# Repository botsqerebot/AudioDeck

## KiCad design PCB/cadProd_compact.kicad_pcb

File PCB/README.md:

# Music player PCB: next revision (rev 2)

Everything to change, check and test for rev 2. The main goal is power saving while the player is **off**:

|                  | Off current   | Shelf life on 1000 mAh                                                         |
| ---------------- | ------------- | ------------------------------------------------------------------------------ |
| Rev 1, estimated | ~0.6–1 mA     | ~6 weeks                                                                       |
| Rev 2, target    | **~25–30 µA** | well over a year (in practice the battery's own self-discharge sets the limit) |

The estimates come from datasheet typical values. Measure the real numbers at bring-up (section 6).

---

## 1. Power rails (the new design)

```
BAT ── BQ24074 ── +REG ──┬── TPS7A2033 "Digital_Vol" (EN = VIN, always on) ── AwO_D3v3 ──┬── ESP32-S3
                         │                                                                ├── BQ24074 EN2, pull-ups R9 R10 R11 R12
                         │                                                                └── Q2 AO3401A ── D3v3 (switched) ──┬── SD card + R6 R7
                         │                                                                                                    └── PCM5102 DVDD + CPVDD
                         └── TPS7A2033 "AnaVol" (EN = EN_ANAVOL) ── A3v3 (switched) ──┬── PCM5102 AVDD
                                                                                        └── MAX9722 amp
```

| Rail         | What's on it                                                              | On while the player is off?         |
| ------------ | ------------------------------------------------------------------------- | ----------------------------------- |
| **AwO_D3v3** | ESP32-S3, BQ24074 EN2, R9 (PGOOD), R10 (CHG), R11 (EN), R12 (BOOT)        | Yes                                 |
| **D3v3**     | SD card VDD, R6 (CMD), R7 (DAT0), PCM5102 DVDD (pin 20) and CPVDD (pin 1) | **No**, Q2 switches it off          |
| **A3v3**     | PCM5102 AVDD, MAX9722                                                     | **No**, `EN_ANAVOL` switches it off |

---

## 2. Changes already in the schematic

- [x] Digital regulator changed from MCP1825 to **TPS7A2033** (Iq ~6.5 µA instead of ~120 µA), with EN tied to VIN
- [x] **C24 1 µF** at the digital regulator's VIN
- [x] **C21/C22** (10 µF + 100 nF) at its output
- [x] Always-on rail **AwO_D3v3** split from the switched **D3v3**
- [x] **Q2 AO3401A** high-side switch, with R25 100k gate pull-up (off at boot and in sleep) and R26 10k to the GPIO
- [x] **R5** (SD Det pull-up, ~330 µA with a card in) **removed**. The firmware uses the internal pull-up while awake.
- [x] R6 and R7 (SD pull-ups) moved to switched D3v3, so they can't back-power the card
- [x] PCM5102 DVDD/CPVDD moved to switched D3v3
- [x] R9, R10, R11, R12 and BQ24074 EN2 on AwO_D3v3. EN on the switched rail would hold the ESP32 in reset forever.

---

## 3. Still to do in the schematic

### Must fix

- [x] **C23 (47 nF) from Q2 gate to Q2 source**, side by side with R25. This gives a ~0.5 ms turn-on (10k × 47 nF), so the inrush is about 75 mA instead of a dip that could reset the ESP32. (Gate-to-GND would switch D3v3 on briefly at every power-up.)
- [ ] **Connect the `GPIO` label at R26 to a real pin: IO21 (module pad 23).** IO11 (pad 19), IO12 (pad 20) and IO18 (pad 11) are also free. Avoid the strapping pins IO0, IO3, IO45 and IO46.
- [ ] **Give the two `GPIO` labels separate names.** Same-named labels are one net in KiCad. Use `BAT_SENSE` → IO8 (pad 12) and `D3V3_EN` → IO21 (pad 23).
- [x] **Battery divider on IO8 (module pad 12)** (R5/R27 1 MΩ, C25 100 nF). It's needed for battery %, LED4 (above 60 %) and the low-battery warnings:
    ```
    BAT+ ──[1 MΩ]──┬── IO8
                   ├──[1 MΩ]── GND
                   └──[100 nF]── GND
    ```
    It draws about 2 µA. IO8 is on ADC1.
- [ ] **Make thermal refes for the `GND` on `LEDs` and Battery**
- [ ] **Battery connector** Make the battery connector fit a JST connection

### Check against datasheets

- [ ] **BQ24074 TMR (pin 14) and ITERM (pin 15)** are unconnected. Check what that means for the safety timer and the termination current, and tie them as intended.
- [ ] **BQ24074 TS:** R8 is a fixed 10k to GND, so temperature protection is off. For a LiPo in a closed case, consider a pack with a 10k NTC wired to TS.
- [ ] **TPS7A2033 output capacitance:** confirm that 10 µF + 100 nF on each output is within the stable range. It should be.
- [ ] **AO3401A pinout in the footprint:** 1 = Gate, 2 = Source, 3 = Drain (SOT-23).

### LEDs

- [ ] **Make the schematic and firmware agree on the colours.** Right now they don't:

    | GPIO | Net  | Schematic | Firmware `config.h` |
    | ---- | ---- | --------- | ------------------- |
    | 38   | LED1 | D1 red    | green               |
    | 39   | LED2 | D2 orange | purple              |
    | 40   | LED3 | D3 green  | orange              |
    | 41   | LED4 | D4 purple | blue                |
    | 42   | LED5 | D5 blue   | red                 |

    Decide which colour goes where, then make the schematic, the silkscreen and `config.h` match.

- [ ] Optional: change R13–R21 from 1 kΩ to **2.2–4.7 kΩ**. That's about 1 mA per LED now; higher values are usually still bright enough behind a case.

### Optional

- [ ] **External 1 MΩ pull-up on PLAY** to AwO_D3v3. The firmware could then power down the RTC peripherals in deep sleep, saving a few µA.
- [ ] **MAX17048 fuel gauge** on I2C (e.g. IO11/IO12), if the divider's ~±10 % isn't good enough. It stays accurate while charging and under load, and draws ~4 µA in hibernate. It needs a firmware driver.
- [ ] Remove any leftover symbols that have no footprint (the old AP2112K symbol).

---

## 4. Footprints and BOM

- [ ] **Digital_Vol:** SOT-23-5 for the TPS7A2033 (it was the MCP1825's SOT-223/DDPAK). Pins: 1 VIN, 2 GND, 3 EN, 4 NC, 5 VOUT.
- [ ] **Q2:** SOT-23. Add **C23** and **C24** footprints.
- [ ] **The BOM says µF**, not "yF". KiCad shows µ as y on some values.
- [ ] TPS7A2033 ×2 (digital + analog). The MCP1825 is no longer used.
- [ ] Battery divider: 2 × 1 MΩ, 1 × 100 nF (0402/0603).

---

## 5. Layout

- [ ] **C24** right next to the digital TPS7A2033's VIN pin. **C21/C22** right next to its VOUT.
- [ ] **C23** close to Q2, between its gate and source pads.
- [ ] Keep the ESP32's decoupling (C6, C7, C8) right at the module's 3V3 pin.
- [ ] **C1/C2** (SD decoupling) close to the SD socket, on D3v3.
- [ ] Battery divider close to IO8, away from the I2S and SD clock traces. The 1 MΩ node is high-impedance and picks up noise.
- [ ] Short, wide traces from Q2 to the SD card VDD.

---

## 6. Bring-up tests

1. **Rails:** power from the battery only. AwO_D3v3 should be 3.3 V. **D3v3 and A3v3 should be 0 V** until the firmware turns them on.
2. **Boot:** the ESP32 starts every time (if it doesn't, EN/R11 is on the wrong rail). Hold Play for 3 s to turn on.
3. **Inrush:** with a scope on AwO_D3v3, the firmware switches D3v3 on. The dip must stay above about 3.0 V, and the ESP32 must not reset.
4. **SD and audio:** cards mount, music plays, and there's no pop at power-on.
5. **Off current:** power off, then put a multimeter (µA range) in series with the battery. Target **~25–30 µA**. If it's much higher:
    - Is D3v3 really 0 V?
    - Is any ESP32 pin driving high into the SD card or DAC?
    - Are the LEDs off?
6. **Charging:** plug in USB. The orange LED lights while charging, also while the player is off. Unplugged, there's no wake loop.
7. **Battery %:** compare Settings > Battery with a multimeter on BAT+ (around 4.2 V full, 3.7 V about 50 %).
8. **LEDs:** check each colour against the table in section 3.

---

## 7. Firmware changes needed for rev 2

These go into `flac_player_4/flac_player/` once the board exists. They're not done yet; ask when the GPIO is final.

- [ ] `config.h`: new `PIN_D3V3_EN 21` (or whichever pin you choose). LOW = D3v3 on.
- [ ] Boot: drive `PIN_D3V3_EN` LOW, wait ~5 ms, then start the SD card.
- [ ] Before deep sleep: drive **all** SD pins (CS, CLK, MOSI, MISO) and I2S pins **LOW**, then set `PIN_D3V3_EN` HIGH and hold it.
    - Rev 1 holds SD CS _high_ in sleep. On rev 2 that would push current into the unpowered card through its protection diodes.
- [ ] `PIN_BAT_ADC 8`. This turns on Settings > Battery, LED4 above 60 %, the red low-battery LED and the "Battery low" / "Battery critical" warnings. That code is already written.
- [ ] LED pin colours in `config.h` to match section 3.

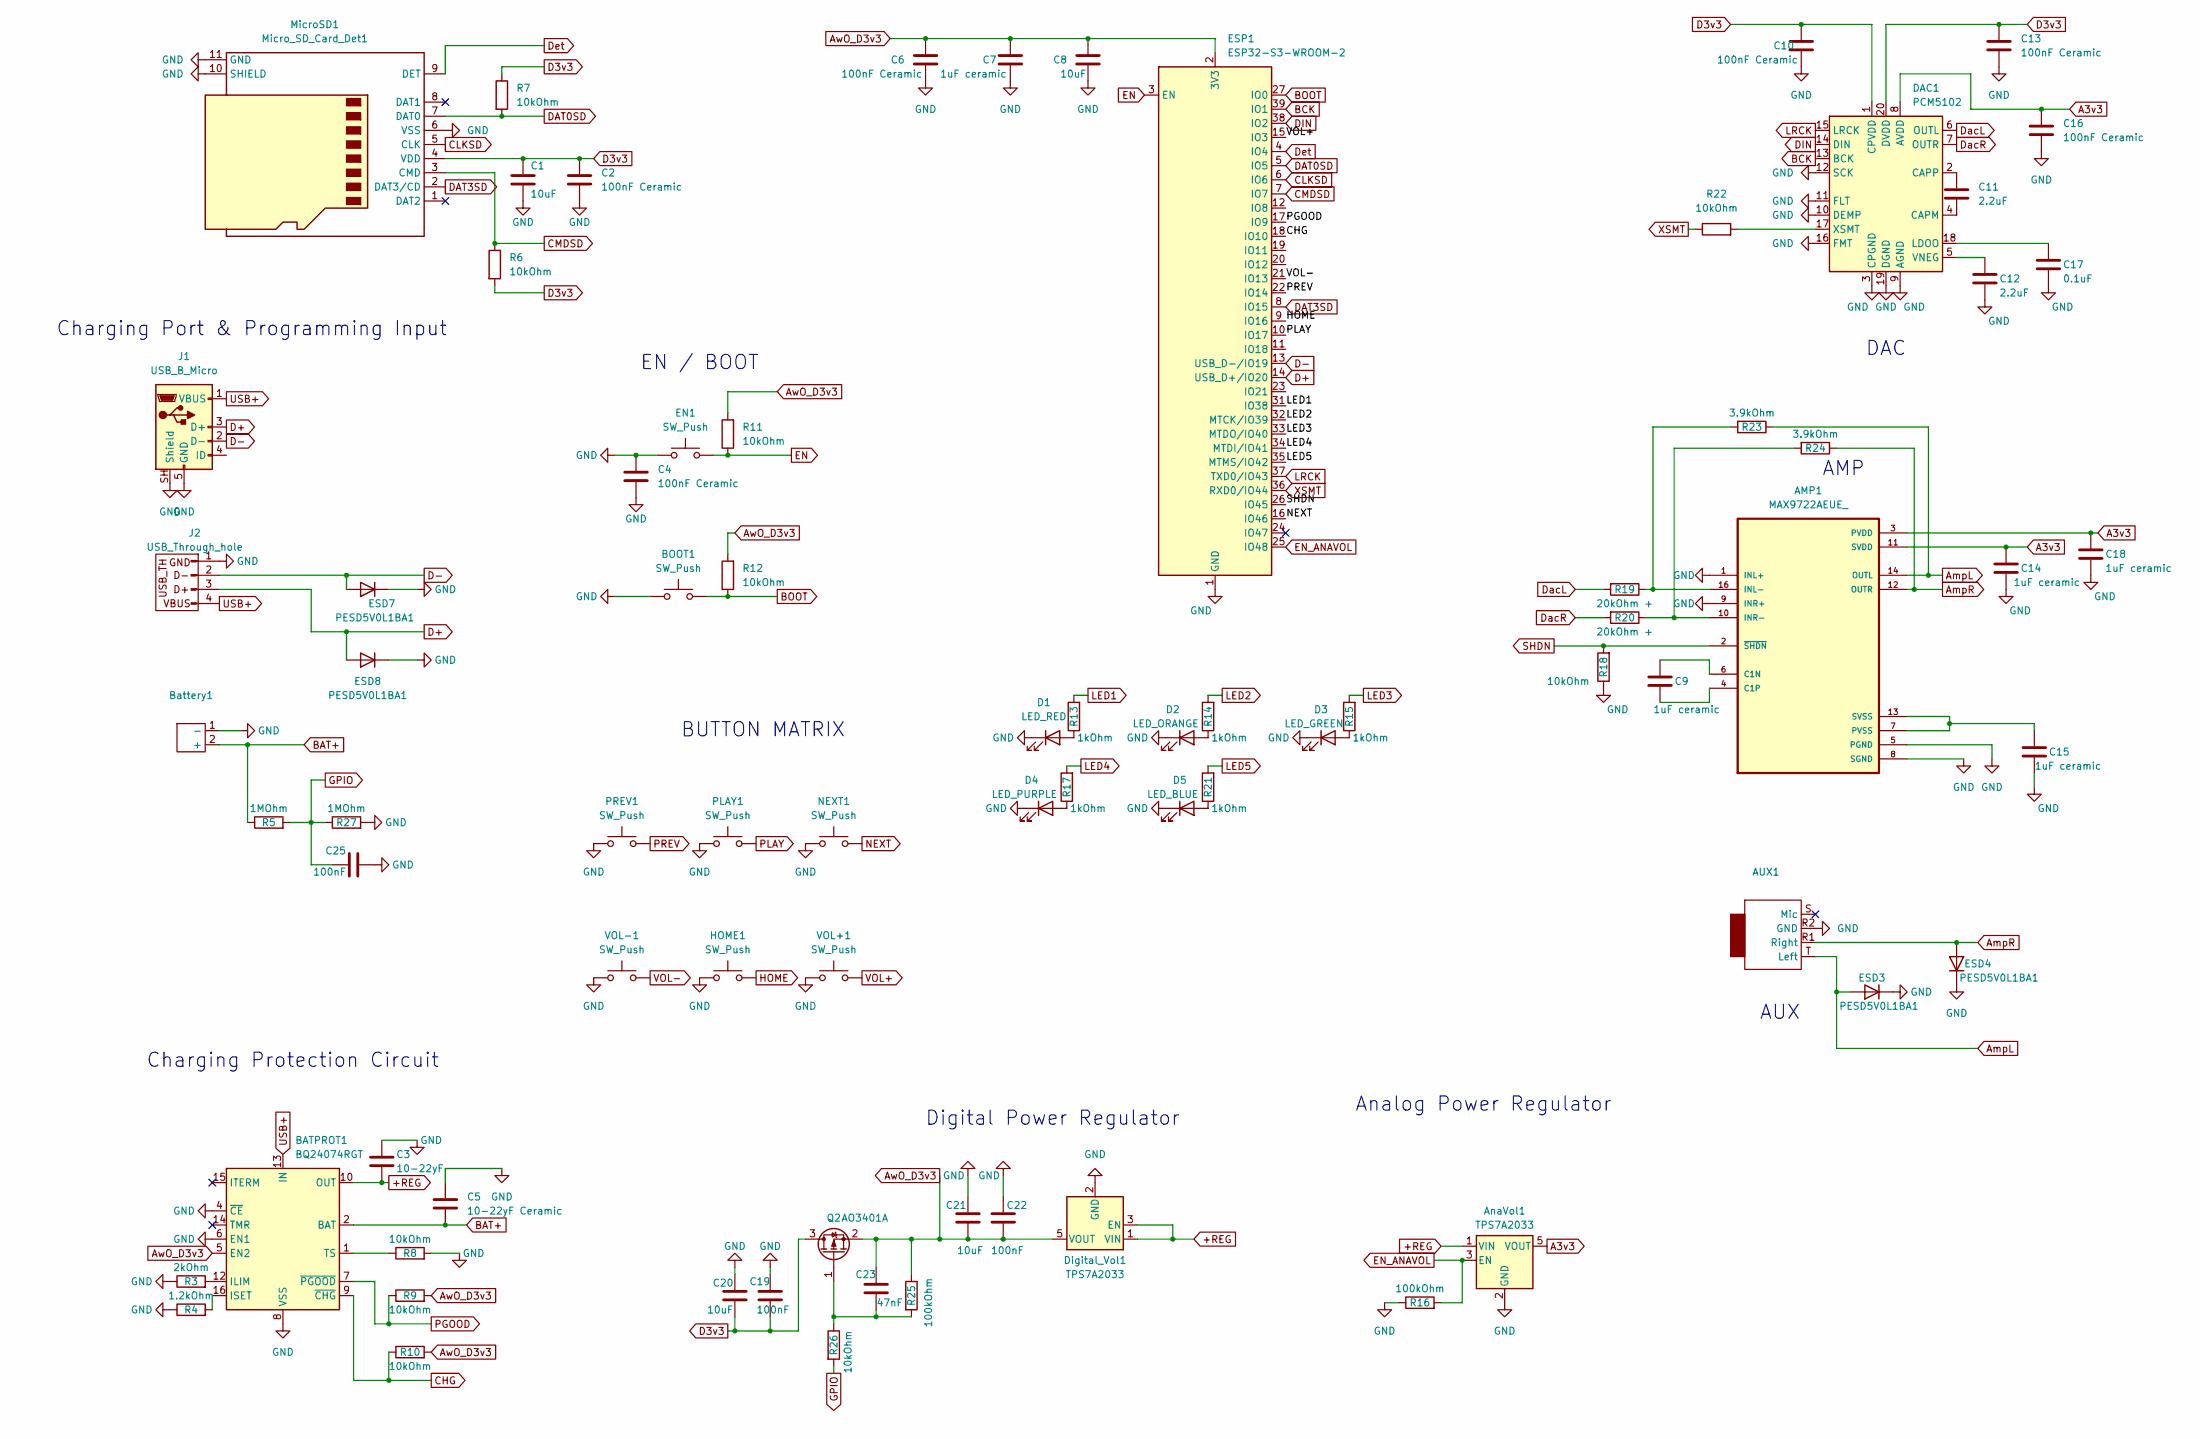
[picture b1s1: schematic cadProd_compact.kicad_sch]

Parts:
AMP1: MAX9722AEUE_; SOP65P640X110-16N
AUX1: Jack_3.5mm_PJ320D_Horizontal
AnaVol1: TPS7A2033; SOT-23-5
BATPROT1: BQ24074RGT; VQFN-16-1EP_3x3mm_P0.5mm_EP1.8x1.8mm
BOOT1: SW_Push; SW_Push_SPST_NO_Alps_SKRK
Battery1: JST_PH_B2B-PH-K_1x02_P2.00mm_Vertical
C1, C8, C20, C21: 10uF; C_0805_2012Metric_Pad1.18x1.45mm_HandSolder
C2, C4, C6, C10, C13, C16: 100nF Ceramic; C_0805_2012Metric_Pad1.18x1.45mm_HandSolder
C3: 10-22yF; C_0805_2012Metric_Pad1.18x1.45mm_HandSolder
C5: 10-22yF Ceramic; C_0805_2012Metric_Pad1.18x1.45mm_HandSolder
C7, C9, C14, C15, C18: 1uF ceramic; C_0805_2012Metric_Pad1.18x1.45mm_HandSolder
C11, C12: 2.2uF; C_0805_2012Metric_Pad1.18x1.45mm_HandSolder
C17: 0.1uF; C_0805_2012Metric_Pad1.18x1.45mm_HandSolder
C19, C22, C25: 100nF; C_0805_2012Metric_Pad1.18x1.45mm_HandSolder
C23: 47nF; C_0805_2012Metric_Pad1.18x1.45mm_HandSolder
D1: LED_RED; LED_0805_2012Metric_Pad1.15x1.40mm_HandSolder
D2: LED_ORANGE; LED_0805_2012Metric_Pad1.15x1.40mm_HandSolder
D3: LED_GREEN; LED_0805_2012Metric_Pad1.15x1.40mm_HandSolder
D4: LED_PURPLE; LED_0805_2012Metric_Pad1.15x1.40mm_HandSolder
D5: LED_BLUE; LED_0805_2012Metric_Pad1.15x1.40mm_HandSolder
DAC1: PCM5102; TSSOP-20_4.4x6.5mm_P0.65mm
Digital_Vol1: TPS7A2033; SOT-23-5
EN1: SW_Push; SW_Push_SPST_NO_Alps_SKRK
ESD3, ESD4, ESD7, ESD8: PESD5V0L1BA1; D_SOD-323
ESP1: ESP32-S3-WROOM-2
HOME1: SW_Push; SW_SPST_SKQG_WithStem
J1: USB_B_Micro; USB_Micro-B_Wuerth_629105150521
J2: USB_Through_hole; PinHeader_1x04_P2.54mm_Vertical_USB
MicroSD1: Micro_SD_Card_Det1; microSD_HC_Hirose_DM3AT-SF-PEJM5
NEXT1: SW_Push; SW_SPST_SKQG_WithStem
PLAY1: SW_Push; SW_SPST_SKQG_WithStem
PREV1: SW_Push; SW_SPST_SKQG_WithStem
Q2: AO3401A; SOT-23
R3: 2kOhm; R_0805_2012Metric_Pad1.20x1.40mm_HandSolder
R4: 1.2kOhm; R_0805_2012Metric_Pad1.20x1.40mm_HandSolder
R5, R27: 1MOhm; R_0805_2012Metric_Pad1.20x1.40mm_HandSolder
R6, R7, R8, R9, R10, R11, R12, R18, R22, R26: 10kOhm; R_0805_2012Metric_Pad1.20x1.40mm_HandSolder
R13, R14, R15, R17, R21: 1kOhm; R_0805_2012Metric_Pad1.20x1.40mm_HandSolder
R16, R25: 100kOhm; R_0805_2012Metric_Pad1.20x1.40mm_HandSolder
R19, R20: 20kOhm +; R_0805_2012Metric_Pad1.20x1.40mm_HandSolder
R23, R24: 3.9kOhm; R_0805_2012Metric_Pad1.20x1.40mm_HandSolder
VOL+1: SW_Push; SW_SPST_SKQG_WithStem
VOL-1: SW_Push; SW_SPST_SKQG_WithStem

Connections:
+REG: AnaVol1.1 (VIN), BATPROT1.10 (OUT), BATPROT1.11 (OUT), C3.2, Digital_Vol1.1 (VIN), Digital_Vol1.3 (EN)
A3v3: AMP1.3 (PVDD), AMP1.11 (SVDD), AMP1.15 (SVDD), AnaVol1.5 (VOUT), C14.1, C16.1, C18.1, DAC1.8 (AVDD); also elsewhere on the board
AmpL: AMP1.14 (OUTL), AUX1.T (Left), ESD3.2 (A), R23.1
AmpR: AMP1.12 (OUTR), AUX1.R1 (Right), ESD4.2 (A), R24.1
AwO_D3v3: BATPROT1.5 (EN2), C6.1, C7.1, C8.1, C21.2, C22.2, C23.1, Digital_Vol1.5 (VOUT), ESP1.2 (3V3), Q2.2 (S), R9.2, R10.2, R11.2, R12.2, R25.1
BAT+: BATPROT1.2 (BAT), BATPROT1.3 (BAT), Battery1.2 (+), C5.2, R5.1
BCK: DAC1.13 (BCK), ESP1.39 (IO1)
BOOT: BOOT1.2, ESP1.27 (IO0), R12.1
CHG: BATPROT1.9 (~CHG), ESP1.18 (IO10), R10.1
CLKSD: ESP1.6 (IO6), MicroSD1.5 (CLK)
CMDSD: ESP1.7 (IO7), MicroSD1.3 (CMD), R6.1
D3v3: C1.1, C2.1, C10.1, C13.1, C19.2, C20.2, DAC1.1 (CPVDD), DAC1.20 (DVDD), MicroSD1.4 (VDD), Q2.3 (D), R6.2, R7.1
D+: ESD8.2 (A), ESP1.14 (USB_D+/IO20), J1.3 (D+), J2.3
D-: ESD7.2 (A), ESP1.13 (USB_D-/IO19), J1.2 (D-), J2.2 (D-)
DAT0SD: ESP1.5 (IO5), MicroSD1.7 (DAT0), R7.2
DAT3SD: ESP1.8 (IO15), MicroSD1.2 (DAT3/CD)
DIN: DAC1.14 (DIN), ESP1.38 (IO2)
DacL: DAC1.6 (OUTL), R19.2
DacR: DAC1.7 (OUTR), R20.2
Det: ESP1.4 (IO4), MicroSD1.9 (DET)
EN: EN1.2, ESP1.3 (EN), R11.1
EN_ANAVOL: AnaVol1.3 (EN), ESP1.25 (IO48), R16.2
GND: AMP1.1 (INL+), AMP1.5 (PGND), AMP1.8 (SGND), AMP1.9 (INR+), AUX1.R2 (GND), AnaVol1.2 (GND), BATPROT1.4 (~CE), BATPROT1.6 (EN1), BATPROT1.8 (VSS), BATPROT1.17 (VSS), BOOT1.1, Battery1.1 (-), C1.2, C2.2, C3.1, C4.1, C4.2, C5.1, C6.2, C7.2, C8.2, C10.2, C12.2, C13.2, C14.2, C15.2, C16.2, C17.2, C18.2, C19.1, C20.1, C21.1, C22.1, C25.2, D1.1 (K), D2.1 (K), D3.1 (K), D4.1 (K), D5.1 (K), DAC1.3 (CPGND), DAC1.9 (AGND), DAC1.10 (DEMP), DAC1.11 (FLT), DAC1.12 (SCK), DAC1.16 (FMT), DAC1.19 (DGND), Digital_Vol1.2 (GND), EN1.1, ESD3.1 (K), ESD4.1 (K), ESD7.1 (K), ESD8.1 (K), ESP1.1 (GND), ESP1.40 (GND), ESP1.41 (GND), HOME1.1, J1.5 (GND), J1.SH (Shield), J2.1, MicroSD1.6 (VSS), MicroSD1.10 (SHIELD), MicroSD1.11 (GND), NEXT1.1, PLAY1.1, PREV1.1, R3.1, R4.1, R8.2, R16.1, R18.1, R27.2, VOL+1.1, VOL-1.1
GPIO: C25.1, R5.2, R26.2, R27.1
HOME: ESP1.9 (IO16), HOME1.2
LED1: ESP1.31 (IO38), R13.2
LED2: ESP1.32 (MTCK/IO39), R14.2
LED3: ESP1.33 (MTDO/IO40), R15.2
LED4: ESP1.34 (MTDI/IO41), R17.2
LED5: ESP1.35 (MTMS/IO42), R21.2
LRCK: DAC1.15 (LRCK), ESP1.37 (TXD0/IO43)
NEXT: ESP1.16 (IO46), NEXT1.2
unnamed: AMP1.6 (C1N), C9.1
unnamed: AMP1.4 (C1P), C9.2
unnamed: AMP1.16 (INL-), R19.1, R23.2
unnamed: AMP1.10 (INR-), R20.1, R24.2
unnamed: AMP1.7 (PVSS), AMP1.13 (SVSS), C15.1
unnamed: BATPROT1.12 (ILIM), R3.2
unnamed: BATPROT1.16 (ISET), R4.2
unnamed: BATPROT1.1 (TS), R8.1
unnamed: D1.2 (A), R13.1
unnamed: D2.2 (A), R14.1
unnamed: D3.2 (A), R15.1
unnamed: D4.2 (A), R17.1
unnamed: D5.2 (A), R21.1
unnamed: C11.2, DAC1.4 (CAPM)
unnamed: C11.1, DAC1.2 (CAPP)
unnamed: C17.1, DAC1.18 (LDOO)
unnamed: C12.1, DAC1.5 (VNEG)
unnamed: DAC1.17 (XSMT), R22.2
unnamed: C23.2, Q2.1 (G), R25.2, R26.1
PGOOD: BATPROT1.7 (~PGOOD), ESP1.17 (IO9), R9.1
PLAY: ESP1.10 (IO17), PLAY1.2
PREV: ESP1.22 (IO14), PREV1.2
SHDN: AMP1.2 (~SHDN), ESP1.26 (IO45), R18.2
USB+: BATPROT1.13 (IN), J1.1 (VBUS), J2.4
VOL+: ESP1.15 (IO3), VOL+1.2
VOL-: ESP1.21 (IO13), VOL-1.2
XSMT: ESP1.36 (RXD0/IO44), R22.1

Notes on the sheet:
Charging Port & Programming Input
BUTTON MATRIX
EN / BOOT
Charging Protection Circuit
AMP
DAC
AUX
Analog Power Regulator
Digital Power Regulator

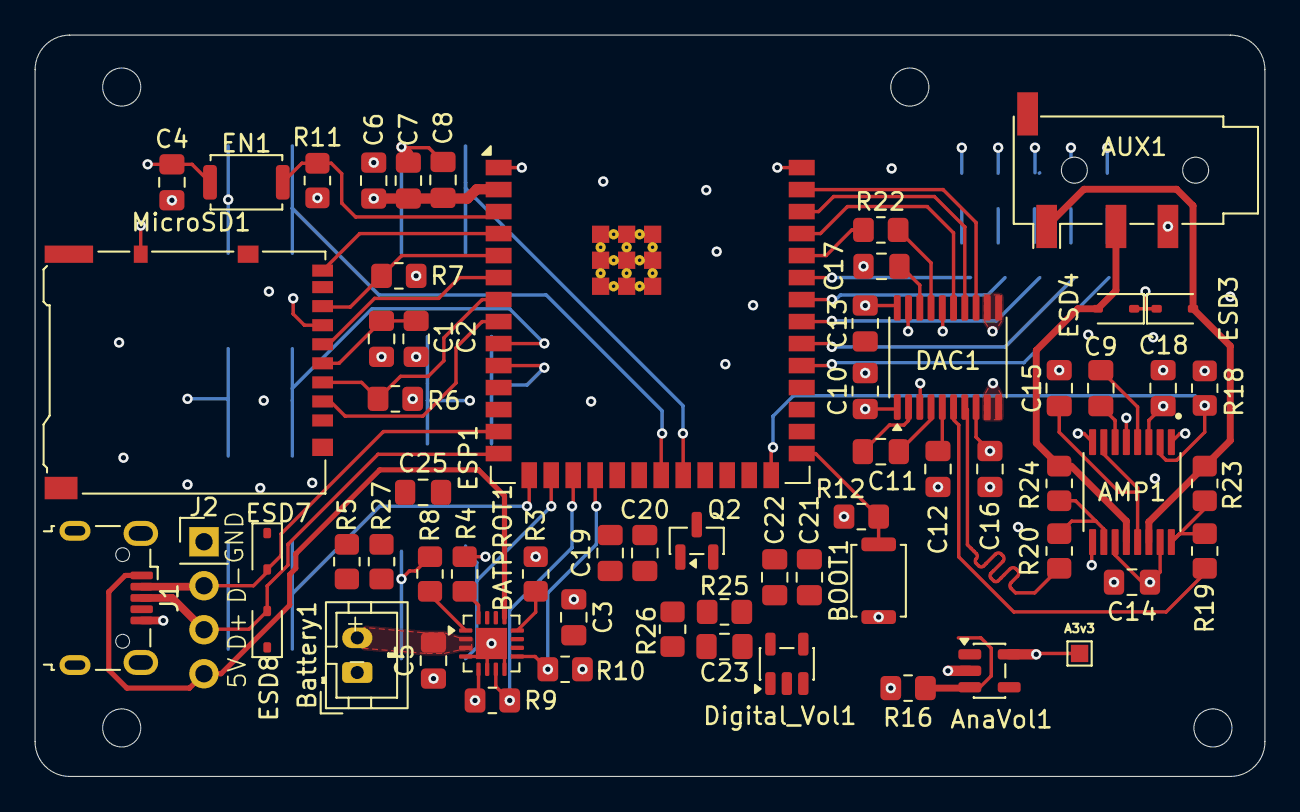
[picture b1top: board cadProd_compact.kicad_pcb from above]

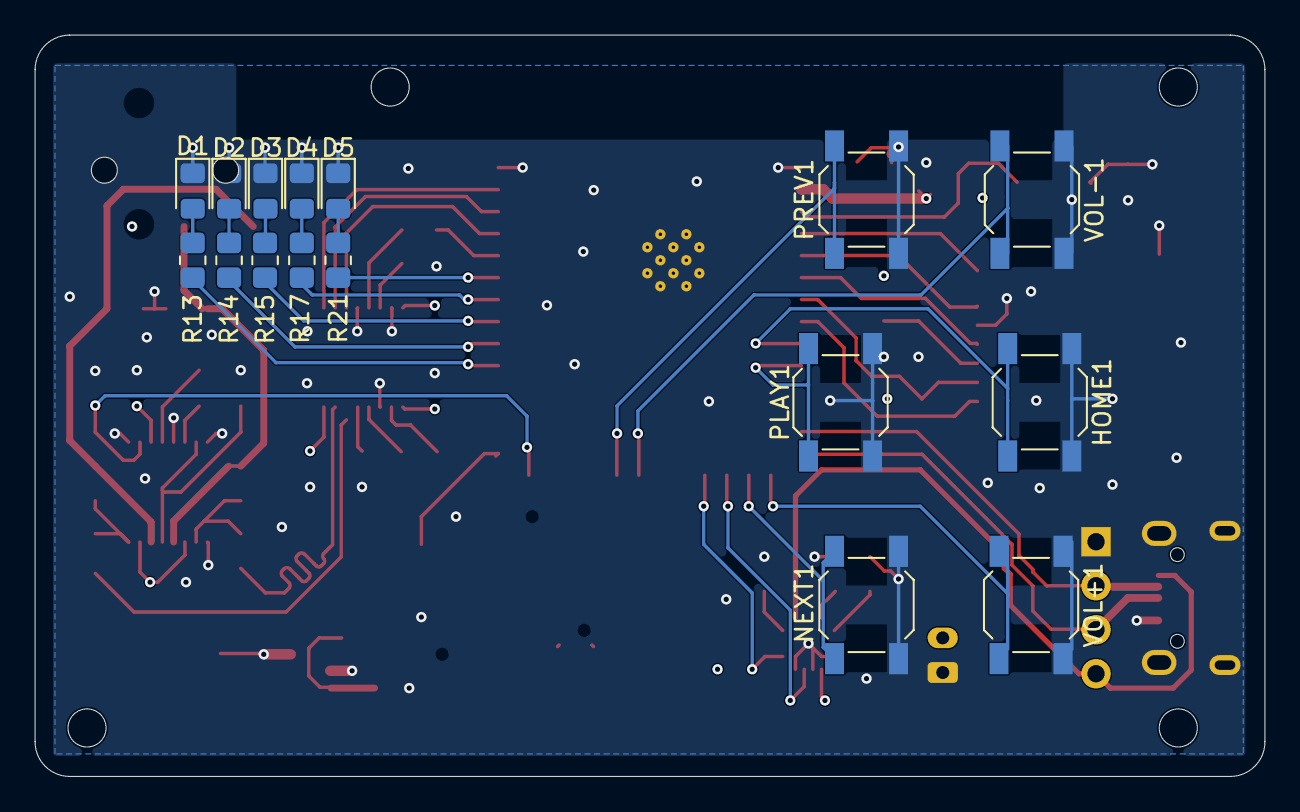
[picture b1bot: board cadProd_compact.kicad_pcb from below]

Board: 4 copper layers, 71.0 x 42.8 mm, 79 parts (16 on the bottom side), 59 nets.

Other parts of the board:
A3v3: TestPoint_Pad_1.0x1.0mm

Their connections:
A3v3: A3v3.1; also elsewhere on the board

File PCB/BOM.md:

# Bill of materials (rev 2)

Read from `cadProd_compact.kicad_sch` (saved 2026-10-15 09:16). Every resistor, capacitor and LED uses the **0805** hand-solder footprint.

## Capacitors (25)

| Value      | Qty    | References                                    | Notes                                              |
| ---------- | ------ | --------------------------------------------- | -------------------------------------------------- |
| **100 nF** | **10** | C2, C4, C6, C10, C13, C16, C17, C19, C22, C25 | C17 is written as "0.1uF", which is the same value |
| **10 µF**  | **6**  | C1, C3, C5, C8, C20, C21                      |                                                    |
| **1 µF**   | **6**  | C7, C9, C14, C15, C18, C24                    |                                                    |
| **2.2 µF** | **2**  | C11, C12                                      | PCM5102 charge pump / LDOO                         |
| **47 nF**  | **1**  | C23                                           | Q2 soft start                                      |

Ceramic X5R/X7R, 6.3 V or more (10 V gives more margin for the 10–22 µF parts).

## Resistors (27)

| Value      | Qty    | References                                   | What for                                                             |
| ---------- | ------ | -------------------------------------------- | -------------------------------------------------------------------- |
| **10 kΩ**  | **10** | R6, R7, R8, R9, R10, R11, R12, R18, R22, R26 | SD pull-ups, BQ24074 TS, PGOOD/CHG, EN/BOOT, amp SHDN, XSMT, Q2 gate |
| **1 kΩ**   | **5**  | R13, R14, R15, R17, R21                      | LEDs (2.2–4.7 kΩ also works and saves power)                         |
| **1 MΩ**   | **2**  | R5, R27                                      | Battery divider                                                      |
| **100 kΩ** | **2**  | R16, R25                                     | EN_ANAVOL pull-down, Q2 gate pull-up                                 |
| **20 kΩ**  | **2**  | R19, R20                                     | Amp input                                                            |
| **5.1 kΩ** | **2**  | R1, R2                                       | USB-C CC1/CC2                                                        |
| **3.9 kΩ** | **2**  | R23, R24                                     | Amp feedback                                                         |
| **2 kΩ**   | **1**  | R3                                           | BQ24074 ILIM                                                         |
| **1.2 kΩ** | **1**  | R4                                           | BQ24074 ISET (charge current)                                        |

## ICs and transistors

| Part                     | Qty | References                         | Package        |
| ------------------------ | --- | ---------------------------------- | -------------- |
| ESP32-S3-WROOM-2 (N16R8) | 1   | ESP1                               | Module         |
| BQ24074RGT               | 1   | BATPROT1                           | VQFN-16 3×3 mm |
| TPS7A2033                | 2   | Digital_Vol, AnaVol1               | SOT-23-5       |
| PCM5102                  | 1   | DAC1                               | TSSOP-20       |
| MAX9722AEUE              | 1   | AMP1                               | TSSOP-16       |
| AO3401A (P-MOSFET)       | 1   | Q2                                 | SOT-23         |
| PESD5V0L1BA1 (ESD)       | 6   | ESD1, ESD2, ESD3, ESD4, ESD7, ESD8 | SOD-323        |

## LEDs (0805)

| Colour | Qty | Reference |
| ------ | --- | --------- |
| Red    | 1   | D1        |
| Orange | 1   | D2        |
| Green  | 1   | D3        |
| Purple | 1   | D4        |
| Blue   | 1   | D5        |

## Buttons and connectors

| Part                                   | Qty | References                               | Footprint                          |
| -------------------------------------- | --- | ---------------------------------------- | ---------------------------------- |
| Push button with stem (Alps SKQG)      | 6   | HOME1, NEXT1, PLAY1, PREV1, VOL+1, VOL-1 | SW_SPST_SKQG_WithStem              |
| Small push button (Alps SKRK)          | 2   | BOOT1, EN1                               | SW_Push_SPST_NO_Alps_SKRK          |
| USB-C receptacle (GCT USB4105)         | 1   | USBC1                                    | USB4105 16P                        |
| Micro-USB (Würth 629105150521)         | 1   | J1                                       |                                    |
| 1×4 pin header, 2.54 mm (USB)          | 1   | J2                                       |                                    |
| microSD socket (Hirose DM3AT-SF-PEJM5) | 1   | MicroSD1                                 |                                    |
| 3.5 mm jack (PJ-320D)                  | 1   | AUX1                                     |                                    |
| Battery connector (JST)                | 1   | Battery1                                 | **Check the footprint, see below** |

## Totals

| Type       | Unique values | Parts |
| ---------- | ------------- | ----- |
| Capacitors | 6             | 25    |
| Resistors  | 9             | 27    |
| Everything |               | 84    |

## Check before ordering

- **Battery1 footprint is `Crystal:Resonator-2Pin_W6.0mm_H3.0mm`.** That's a crystal footprint, not a JST battery connector. Change it to the matching JST footprint, e.g. `Connector_JST:JST_PH_S2B-PH-K_1x02_P2.00mm_Horizontal` for JST-PH.
- **C3/C5 "10-22yF":** set one real value (the "y" is how KiCad shows µ).
- **Both TPS7A2033s use the `AP2112K-3.3` symbol.** Its pinout (1 VIN, 2 GND, 3 EN, 4 NC, 5 VOUT) matches the TPS7A2033 in SOT-23-5, so it's fine. Only the symbol name is different.
- **AUX1 has no value.** Fill it in (PJ-320D) so it shows in the BOM export.
- **Spares:** 0805 parts are easy to lose when hand soldering. Order a 10–20 % extra of the common values (100 nF, 10 kΩ, 1 µF, 10 µF).

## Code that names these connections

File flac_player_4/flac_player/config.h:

// config.h — pins, paths and tuning for the FLAC player
#pragma once

// ---------- Pins (from your PCB) ----------
#define PIN_I2S_BCK     1
#define PIN_I2S_DIN     2
#define PIN_I2S_LRCK    43
#define PIN_DAC_XSMT    44   // PCM5102 soft mute: HIGH = play, LOW = mute
#define PIN_AMP_SHDN    45   // MAX9722 SHDN: HIGH = on
#define PIN_LDO_EN      48   // TPS7A2033 EN: HIGH = on

#define PIN_SD_DET      4
#define PIN_SD_MISO     5
#define PIN_SD_CLK      6
#define PIN_SD_MOSI     7
#define PIN_SD_CS       15

#define PIN_CHG_PGOOD   9
#define PIN_CHG_STAT    10

#define PIN_BTN_VOLUP   3
#define PIN_BTN_VOLDN   13
#define PIN_BTN_PREV    14
#define PIN_BTN_HOME    16
#define PIN_BTN_PLAY    17
#define PIN_BTN_NEXT    46

// Status LEDs (GPIO 38-42: green, purple, orange, blue, red)
#define PIN_LED_GREEN   38           // LED1: on while the player is on
#define PIN_LED_PURPLE  39           // LED2: not used yet, kept off
#define PIN_LED_ORANGE  40           // LED3: charging
#define PIN_LED_BLUE    41           // LED4: battery above 60 % (needs PIN_BAT_ADC)
#define PIN_LED_RED     42           // LED5: low battery (needs PIN_BAT_ADC)
#define LED_ACTIVE_HIGH 1            // 1 = pin HIGH lights the LED

// Battery sense: ADC pin on a divider from the battery (-1 = none).
// The board has none yet; GPIO 8 is free and ADC-capable: 1M from BAT+ to GPIO 8, 1M from
// GPIO 8 to GND, 100 nF from GPIO 8 to GND (draws ~2 uA, so it doesn't drain the battery).
// Without it the red LED, LED4, Settings > Battery and the low-battery warnings stay off.
#define PIN_BAT_ADC     -1
#define HAS_BATTERY     (PIN_BAT_ADC >= 0)
#define BAT_DIVIDER     2.0f         // battery volts / pin volts (2.0 for two equal resistors)
#define BAT_LOW_V       3.45f        // red LED below this
#define BAT_LED4_PCT    60           // LED4 on above this
#define BAT_WARN_PCT    15           // says "Battery low" once
#define BAT_CRIT_PCT    3            // says "Battery critical" and powers off

// Power button holds
#define POWER_OFF_HOLD_MS  3000      // hold Home this long to power off
#define POWER_ON_HOLD_MS   3000      // hold Play this long to power on
#define CHARGE_CHECK_SEC   30        // while off and charging: wake this often to update the orange LED
#define AUTO_OFF_MIN       10        // power off after this long with nothing playing and no button pressed

#define BUTTON_ACTIVE_LOW 1          // buttons pull the pin to GND
#define SD_SPI_HZ       40000000     // drop to 20000000 if the card gives errors

// ---------- SD layout ----------
#define MUSIC_DIR       "/Music"
#define VOICE_DIR       "/Voices"
#define VOICE_MENU_DIR  "/Voices/Menu"
#define VOICE_LIB_DIR   "/Voices/Library"
#define SYSTEM_DIR      "/System"
#define LIBRARY_JSON    "/System/library.json"
#define STATE_JSON      "/System/state.json"
#define PLAYLIST_DIR    "/Playlists"   // <name>.m3u8, one /Music/... path per line (made by Voice Studio)

// ---------- Audio ----------
#define READ_AHEAD_BYTES   (32 * 1024)   // per track, lives in PSRAM
#define I2S_DMA_BUFFERS    8
#define I2S_DMA_BYTES      2304
#define VOLUME_STEPS       80            // one Vol+/Vol- press = one step
#define VOLUME_DEFAULT     40
#define MAX_GAIN           1.0f          // gain at full volume (ESP8266Audio allows up to 4.0)
#define VOLUME_SAFE_START  40            // at power-on the volume is lowered to this if it was higher
#define FADE_MS            150           // Settings > Soft fade: pause/resume fade length
#define DUCK_LEVEL         0.25f         // Settings > Duck music: music level under a voice clip (-12 dB)
#define DUCK_MS            60            // how fast the music dips and comes back
#define RESUME_REWIND_SEC  3             // resuming after a long pause (or power-off) starts this much earlier
#define RESUME_REWIND_AFTER_MS 60000     // "long pause"

// ---------- Voice clips (made on the PC by Voice Studio) ----------
#define VOICE_HOVER_DELAY_MS   150   // wait after the last press before speaking (old clip is cut at once)
#define VOICE_RESUME_MS        4000  // music resumes this long after the last voice clip (time to keep scrolling)
#define VOICE_MAX_CHARS        120   // clip names are a hash of the first 120 chars (matches Voice Studio)

// ---------- Buttons ----------
#define BTN_PRESS_MS       25        // press must be stable this long
#define BTN_RELEASE_MS     60        // release must be stable this long (stops double steps)
#define LONG_PRESS_MS      900       // hold for shuffle, repeat and home (long enough to avoid accidents)
#define REPEAT_DELAY_MS    700       // hold Prev/Next this long before it starts auto-scrolling
#define REPEAT_RATE_MS     150
#define BUTTON_DEBUG       1         // print every button event on Serial
#define AUDIO_RATE_DEBUG   1         // print the real I2S output rate on Serial every 10 s
#define HISS_TEST          0         // 1 = DAC stays unmuted while paused: hiss then = analog noise floor
#define STATE_SAVE_MS      5000      // resume position saved this often while playing
#define PREV_RESTART_SEC   3         // Prev after this many seconds restarts the song

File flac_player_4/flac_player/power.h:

// power.h — power off (deep sleep), power on with a long Play press, status LEDs.
//
//  Off:      hold Home 3 s  -> "Powering off", analog regulator, amp and DAC off, deep sleep
//  On:       hold Play 3 s  -> green LED blinks while you hold, then the player starts
//  LEDs:     green = on, orange = charging (also while off), red = low battery,
//            blue (LED4) = battery above 60 %, purple is kept off
//            (red, blue and the battery percent need PIN_BAT_ADC)
//
// While off the ESP32 sleeps. If the charger is plugged in it wakes for a moment every
// 30 s to update the orange LED (BQ24074 CHG pin), otherwise it only wakes when Play is
// pressed or the charger is plugged in.
//
// The SD card and the DAC's digital side stay powered while off (they sit on the always-on
// 3.3 V rail), so before sleeping every pin they can see is parked at a fixed level and held.
// Floating SPI/I2S pins would keep them from going idle.
#pragma once
#include <Arduino.h>
#include <esp_sleep.h>
#include <driver/rtc_io.h>
#include <driver/gpio.h>
#include "config.h"

namespace Power {

static bool redLatched = false, blueOn = false;
static uint32_t lastUpdate = 0;
static float vSmooth = 0;          // smoothed battery volts (0 = no reading yet)
static int percent = -1;           // -1 = unknown (no battery sense)
static bool warned = false;
static uint8_t critCount = 0;

static void led(int pin, bool on) {
  if (pin < 0) return;
  pinMode(pin, OUTPUT);
  digitalWrite(pin, (on == LED_ACTIVE_HIGH) ? HIGH : LOW);
}

static bool charging() { return digitalRead(PIN_CHG_STAT) == LOW; }     // BQ24074 CHG: low while charging
static bool pluggedIn() { return digitalRead(PIN_CHG_PGOOD) == LOW; }   // BQ24074 PGOOD: low with input power

// Battery voltage in volts, 0 if no battery sense pin is configured
static float batteryVolts() {
  if (PIN_BAT_ADC < 0) return 0;
  uint32_t mv = 0;
  for (int i = 0; i < 8; i++) mv += analogReadMilliVolts(PIN_BAT_ADC);
  return mv / 8.0f / 1000.0f * BAT_DIVIDER;
}

// LiPo resting voltage -> percent (linear in between)
static int voltsToPercent(float v) {
  static const float V[] = {3.30f, 3.50f, 3.61f, 3.67f, 3.71f, 3.75f, 3.79f, 3.85f, 3.92f, 4.00f, 4.10f, 4.20f};
  static const int P[] = {0, 5, 10, 20, 30, 40, 50, 60, 70, 80, 90, 100};
  if (v <= V[0]) return 0;
  for (int i = 1; i < 12; i++)
    if (v < V[i]) return P[i - 1] + (int)lroundf((v - V[i - 1]) / (V[i] - V[i - 1]) * (P[i] - P[i - 1]));
  return 100;
}

// Battery percent, -1 without battery sense. Reads high while charging.
static int batteryPercent() { return percent; }

// Pins the always-on SD card and DAC can see (released on wake)
static const int PARKED[] = {PIN_I2S_BCK, PIN_I2S_DIN, PIN_I2S_LRCK, PIN_SD_CS, PIN_SD_CLK, PIN_SD_MOSI, PIN_SD_MISO, PIN_SD_DET};

static void releaseHolds() {
  for (int p : PARKED) gpio_hold_dis((gpio_num_t)p);
  const int pins[] = {PIN_LDO_EN, PIN_AMP_SHDN, PIN_DAC_XSMT, PIN_LED_GREEN, PIN_LED_PURPLE, PIN_LED_ORANGE, PIN_LED_BLUE, PIN_LED_RED};
  for (int p : pins) if (p >= 0) gpio_hold_dis((gpio_num_t)p);
  gpio_deep_sleep_hold_dis();
  rtc_gpio_deinit((gpio_num_t)PIN_BTN_PLAY);
  rtc_gpio_deinit((gpio_num_t)PIN_CHG_PGOOD);
}

static void holdLow(int pin) {
  if (pin < 0) return;
  pinMode(pin, OUTPUT);
  digitalWrite(pin, LOW);
  gpio_hold_en((gpio_num_t)pin);
}
static void holdHigh(int pin) {
  pinMode(pin, OUTPUT);
  digitalWrite(pin, HIGH);
  gpio_hold_en((gpio_num_t)pin);
}
static void holdInput(int pin) {     // high impedance, no internal pull
  pinMode(pin, INPUT);
  gpio_hold_en((gpio_num_t)pin);
}

// SD and I2S pins to fixed levels. Call after SD.end() / the engine's shutdown().
static void parkBusPins() {
  holdLow(PIN_I2S_BCK);              // no clock: the PCM5102 powers down, inputs not floating
  holdLow(PIN_I2S_DIN);
  holdLow(PIN_I2S_LRCK);
  holdHigh(PIN_SD_CS);               // card deselected (no pull-up on the board)
  holdLow(PIN_SD_CLK);
  holdInput(PIN_SD_MOSI);            // R6 and R7 pull these up: driving them low would cost 330 uA each
  holdInput(PIN_SD_MISO);
  holdInput(PIN_SD_DET);             // R5 pulls it up, the internal pull-up is not needed
}

// Everything off, then deep sleep. Never returns (the next start is a fresh boot).
[[noreturn]] static void sleepNow() {
  pinMode(PIN_CHG_STAT, INPUT_PULLUP);
  pinMode(PIN_CHG_PGOOD, INPUT_PULLUP);
  delay(2);
  bool chg = charging(), plugged = pluggedIn();

  parkBusPins();
  holdLow(PIN_DAC_XSMT);       // DAC muted
  holdLow(PIN_AMP_SHDN);       // amp shut down
  holdLow(PIN_LDO_EN);         // analog regulator off
  led(PIN_LED_GREEN, false);
  led(PIN_LED_PURPLE, false);
  led(PIN_LED_BLUE, false);
  led(PIN_LED_RED, false);
  led(PIN_LED_ORANGE, chg);
  const int leds[] = {PIN_LED_GREEN, PIN_LED_PURPLE, PIN_LED_ORANGE, PIN_LED_BLUE, PIN_LED_RED};
  for (int p : leds) if (p >= 0) gpio_hold_en((gpio_num_t)p);
  gpio_deep_sleep_hold_en();

  // wake on Play (held for 3 s is checked after waking)
  rtc_gpio_init((gpio_num_t)PIN_BTN_PLAY);
  rtc_gpio_set_direction((gpio_num_t)PIN_BTN_PLAY, RTC_GPIO_MODE_INPUT_ONLY);
  rtc_gpio_pullup_en((gpio_num_t)PIN_BTN_PLAY);
  rtc_gpio_pulldown_dis((gpio_num_t)PIN_BTN_PLAY);
  esp_sleep_enable_ext0_wakeup((gpio_num_t)PIN_BTN_PLAY, 0);

  if (plugged) {
    esp_sleep_enable_timer_wakeup((uint64_t)CHARGE_CHECK_SEC * 1000000ULL);   // keep the orange LED right
  } else {
    rtc_gpio_init((gpio_num_t)PIN_CHG_PGOOD);                                 // wake when the charger is plugged in
    rtc_gpio_set_direction((gpio_num_t)PIN_CHG_PGOOD, RTC_GPIO_MODE_INPUT_ONLY);
    rtc_gpio_pullup_en((gpio_num_t)PIN_CHG_PGOOD);
    rtc_gpio_pulldown_dis((gpio_num_t)PIN_CHG_PGOOD);
    esp_sleep_enable_ext1_wakeup(1ULL << PIN_CHG_PGOOD, ESP_EXT1_WAKEUP_ANY_LOW);
  }
  Serial.flush();
  esp_deep_sleep_start();
}

// First thing in setup(). Returns only if the player should start.
static void handleWake() {
  esp_sleep_wakeup_cause_t cause = esp_sleep_get_wakeup_cause();
  releaseHolds();
  pinMode(PIN_CHG_STAT, INPUT_PULLUP);
  pinMode(PIN_CHG_PGOOD, INPUT_PULLUP);
  pinMode(PIN_BTN_PLAY, INPUT_PULLUP);
  // keep the analog side off until we know we're starting
  pinMode(PIN_LDO_EN, OUTPUT);   digitalWrite(PIN_LDO_EN, LOW);
  pinMode(PIN_AMP_SHDN, OUTPUT); digitalWrite(PIN_AMP_SHDN, LOW);
  pinMode(PIN_DAC_XSMT, OUTPUT); digitalWrite(PIN_DAC_XSMT, LOW);
  led(PIN_LED_PURPLE, false);
  led(PIN_LED_BLUE, false);
  led(PIN_LED_RED, false);
  led(PIN_LED_ORANGE, charging());

  if (cause == ESP_SLEEP_WAKEUP_TIMER || cause == ESP_SLEEP_WAKEUP_EXT1) sleepNow();   // charger check only

  if (cause == ESP_SLEEP_WAKEUP_EXT0) {
    // Play must stay down for POWER_ON_HOLD_MS (counted from the wake-up press)
    uint32_t t0 = millis();
    while (millis() < POWER_ON_HOLD_MS) {
      if (digitalRead(PIN_BTN_PLAY) != LOW) {          // let go too early: back to sleep
        if (millis() - t0 > 30) sleepNow();
      } else t0 = millis();
      led(PIN_LED_GREEN, (millis() / 150) % 2);       // blink while counting
      delay(10);
    }
  }
  // Power-on reset (battery connected, USB, reset button) starts straight away
  led(PIN_LED_GREEN, true);
}

// Call from loop(): LEDs follow the charger and battery
static void update() {
  uint32_t now = millis();
  if (now - lastUpdate < 1000) return;
  lastUpdate = now;
  led(PIN_LED_GREEN, true);
  led(PIN_LED_ORANGE, charging());
  float v = batteryVolts();
  if (v > 0.5f) {
    vSmooth = vSmooth > 0 ? vSmooth * 0.9f + v * 0.1f : v;            // music load makes it jump
    percent = voltsToPercent(vSmooth);
    if (!redLatched && vSmooth < BAT_LOW_V) redLatched = true;
    else if (redLatched && vSmooth > BAT_LOW_V + 0.10f) redLatched = false;   // hysteresis, no flicker
    if (!blueOn && percent > BAT_LED4_PCT) blueOn = true;
    else if (blueOn && percent < BAT_LED4_PCT - 2) blueOn = false;
    led(PIN_LED_BLUE, blueOn);
  }
  led(PIN_LED_RED, redLatched);
}

// Call from loop(): BAT_LOW once when the battery gets low, BAT_CRITICAL when it is
// nearly empty (time to save and power off before the SD card browns out)
enum : uint8_t { BAT_OK = 0, BAT_LOW = 1, BAT_CRITICAL = 2 };
static uint8_t lowEvent() {
  static uint32_t lastCheck = 0;
  uint32_t now = millis();
  if (percent < 0 || now - lastCheck < 1000) return BAT_OK;
  lastCheck = now;
  if (pluggedIn()) { warned = false; critCount = 0; return BAT_OK; }
  if (percent <= BAT_CRIT_PCT) { if (++critCount >= 5) return BAT_CRITICAL; }   // 5 s in a row, not a dip
  else critCount = 0;
  if (percent > BAT_WARN_PCT + 5) warned = false;
  if (!warned && percent <= BAT_WARN_PCT) { warned = true; return BAT_LOW; }
  return BAT_OK;
}

}  // namespace Power
